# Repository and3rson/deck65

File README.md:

# Deck65

Homebrew 6502-based single-board computer with WiFi, built-in mechanical keyboard, uSD card adapter, I2C/SPI, EEPROM, & RTC.

- New discussion: <http://forum.6502.org/viewtopic.php?f=6&t=7682>
- Original thread (old SBC version): <http://forum.6502.org/viewtopic.php?f=12&t=7501>

Pull with `git pull --recurse-submodules`.

# Memory map

```
+--------------+-------+------------------+------+------------------------------------------+
| RANGE        | TYPE  | ADDR             | SIZE | Notes                                    |
+--------------+-------+------------------+------+------------------------------------------+
| $0000..$0FFF | RAM   | 0000------------ | 32 K | /EN = A15                                |
| $1000..$1FFF |       | 0001------------ |      | $0000..$1000 - zeropage & video buffer   |
| $2000..$2FFF |       | 0010------------ |      | $1000..$7FFF - programs from SD Card     |
| $3000..$3FFF |       | 0011------------ |      |                                          |
| $4000..$4FFF |       | 0100------------ |      |                                          |
| $5000..$5FFF |       | 0101------------ |      |                                          |
| $6000..$6FFF |       | 0110------------ |      |                                          |
| $7000..$7FFF |       | 0111------------ |      |                                          |
+--------------+-------+------------------+------+------------------------------------------+
| $8000..$8FFF | LOROM | 1000------------ | 16 K | /EN = NAND(A15, NAND(A14))               |
| $9000..$9FFF |       | 1001------------ |      | Contains OS ("MicroREPL")                |
| $A000..$AFFF |       | 1010------------ |      |                                          |
| $B000..$BFFF |       | 1011------------ |      |                                          |
+--------------+-------+------------------+------+------------------------------------------+
| $C000..$CFFF | N/C   | 1100------------ | 4 K  | Unused, may add extra '138 with /GA=/A13 |
+--------------+-------+------------------+------+------------------------------------------+
| $D000..$DFFF | I/O   | 1101------------ | 4 K  | G = A12, /GA = A13, /GB = NAND(A15, A14) |
|              |       | 1101-000-------- | 256B | $D000..$D0FF - RAM banking register      |
|              |       | 1101-001-------- | 256B | $D100..$D1FF - 6522 VIA                  |
|              |       | 1101-010-------- | 256B | $D200..$D2FF - 6551 ACIA                 |
|              |       | 1101-011-------- | 256B | $D300..$D3FF - T6963C LCD (240x64)       |
+--------------+-------+------------------+------+------------------------------------------+
| $E000..$EFFF | HIROM | 1110------------ | 8 K  | /EN = NAND(/NAND(A15, A14), A13)         |
| $F000..$FFFF |       | 1111------------ |      | Contains Kernel ("Kore")                 |
+--------------+-------+------------------+------+------------------------------------------+

LOROM (10xx) || HIROM (111x):
/EN = A15 && (/A14 || (A14 && A13))
/EN = NAND(A15, /A14 || /NAND(A14, A13))
/EN = NAND(A15, NAND(A14, NAND(A14, A13)))
```

# Features

- W65C02, 512 KB RAM (32KB visible to CPU, banked into 4 x 8 KB segments)
- 240x64 LCD display (T6963C)
- Built-in [mechanical PS/2 keyboard](./keyboard), powered by ATmega328P
- Internet! Works through ESP-01
- VIA W65C22<ins>N</ins>(6TPG-14)

  Provides:
  - SPI (used for Micro SD Card adapter)
  - I2C (used for RTC & EEPROM)
  - PS/2 host (used for built-in or external keyboard)
- ACIA W65C51<ins>N</ins>(6TPG-14)n

  Provides:
  - Communication with ESP-01
  - Communication with external devices through pin header
  > Note: I'm using NMOS-compatible versions of VIA & ACIA (<ins>N</ins> suffix) with open-drain /IRQ line.<br />
  > See http://archive.6502.org/datasheets/wdc_w65c22_sep_13_2010.pdf (page 25) for more details.
- Address decoder & underclocking - [ATF16V8B-15PU](./gal)
  > Main crystal is 16 MHz, and the CPU runs at either 8 MHz or 2 MHz.<br />
  > Reason for this is that T6963C LCD can only operate on up to 2.75 MHz.<br />
  > So when CPU needs to acccess the LCD, ATF16V8 divides clock speed by 4, bringing it down to 2 MHz.<br />
  > This is done by implementing a 2-bit counter using registered outputs.
- Memory banking: 74LS670
  > Entire RAM (first 32 KB) is divided into 4 x 8 KB segments.<br />
  > Each segment can use one of its own 16 banks.<br />
  > This allows to selectively bank parts of RAM in and out.<br />
  > Using a machine-tooled socket actually allows to connect JCO-8 or JCO-14 oscillators.
- Traco Power TSR 1-2450 (drop-in replacement for 7805)
  > It runs much cooler than L7805 since it's a switching regulator.<br />
  > I use them a lot, although they are not as cheap as 7805.

V2.0 schematic:

# ROM

Kernel code currently provides the following features:
- Simple REPL shell to monitor memory & run programs
- 128x64 LCD (through VIA)
- PS/2 keyboard (through VIA)
- Micro SD Card in SPI mode (through VIA)
- I2C & SPI support
- Basic FAT16 support - listing root folder, loading/executing programs

# Resources

- [Kicad files](./kicad) - <https://www.kicad.org/>
- [DipTrace PCBs](./diptrace) - <https://diptrace.com/>
- [Circuits](./circuits) (created with [Digital](https://github.com/hneemann/Digital))
- [ROM sources](./rom) (written in 6502 Assembly, requires [cc65](https://cc65.github.io/) compiler)
- [SD Card programs](./sdcard) (written in 6502 C, requires [cc65](https://cc65.github.io/) compiler)
- [Keyboard firmware](./keyboard) (written in C)
- [GAL stuff](./gal) (hexadecimal 7-segment decoder, address decoder, etc using GAL16V8/GAL20V8, includes `galasm` as submodule)
- [Composite video test](./compvid) using ATtiny45 (requires [avra](https://github.com/Ro5bert/avra))

# So what can you do with it?

Playing snake, for example:

# Credits & references
- [6502.org community](forum.6502.org/) - Limitless help & support
- https://www.masswerk.at/6502/6502_instruction_set.html
- https://github.com/4x1md/kicad_libraries - Mini-DIN-6 symbol & footprint
- http://39k.ca/reading-files-from-fat16/
- https://laughtonelectronics.com/Arcana/KimKlone/Kimklone_opcode_mapping.html - cool illegal NOPs
- https://octopart.componentsearchengine.com/part.php?partID=570717&ref=octopart - Aries 28-526-10 footprint
- https://github.com/daprice/keyswitches.pretty - MX switches
- https://components101.com/sites/default/files/component_datasheet/Micro-SD-Card-Module-Datasheet.pdf - MicroSD card module datasheet & dimensions
- http://static.cactus.io/docs/sensors/temp-humidity/mcp9808/25095A.pdf - MCP9808 I2C temperature sensor
- https://ww1.microchip.com/downloads/aemDocuments/documents/MPD/ProductDocuments/DataSheets/24AA512-24LC512-24FC512-512K-Bit-I2C-Serial-EEPROM-20001754Q.pdf

# Links
- 6502 Primer: http://wilsonminesco.com/6502primer/
- Address Selector: https://circuitverse.org/simulator/embed/6502-address-selector
- Read-Write Selector: https://circuitverse.org/simulator/embed/6502-read-write-selector
- SID (HVSC) format: https://gist.github.com/cbmeeks/2b107f0a8d36fc461ebb056e94b2f4d6

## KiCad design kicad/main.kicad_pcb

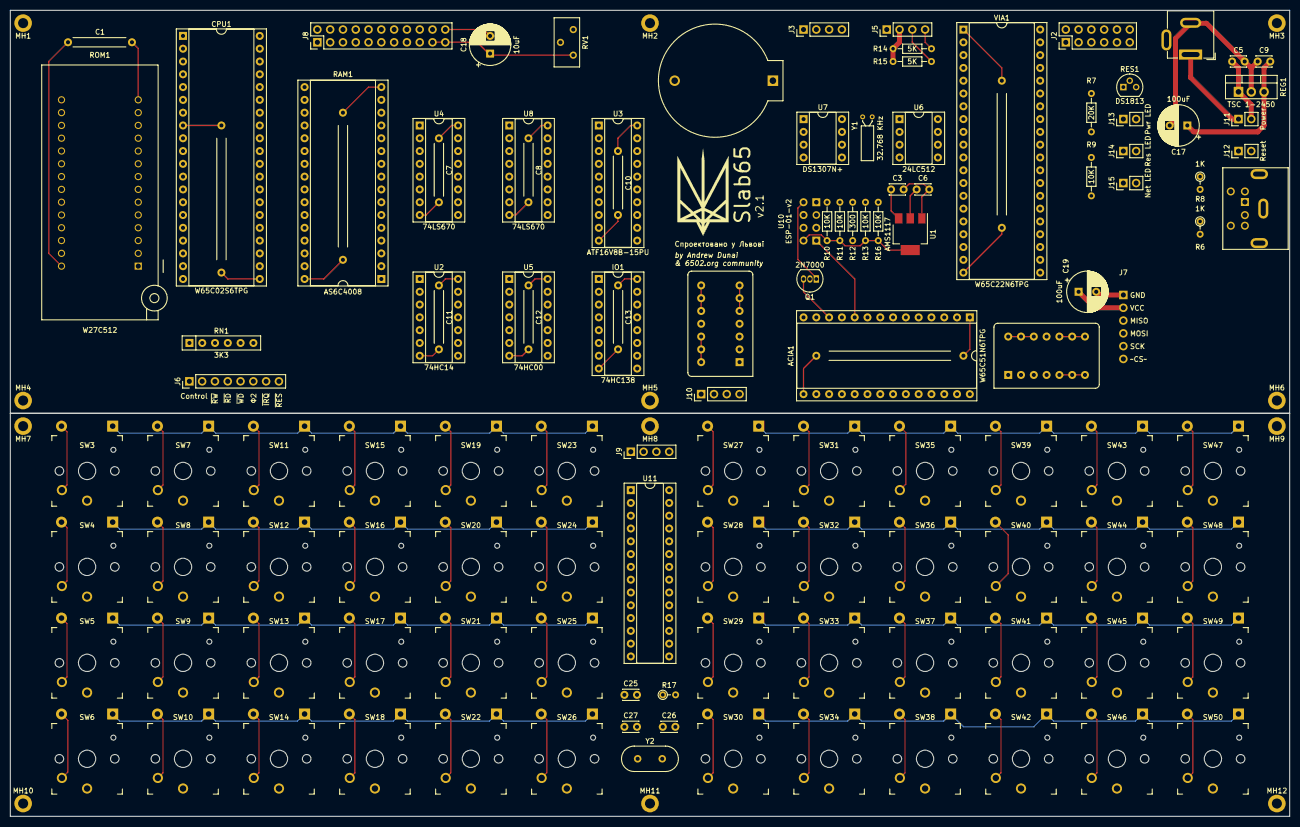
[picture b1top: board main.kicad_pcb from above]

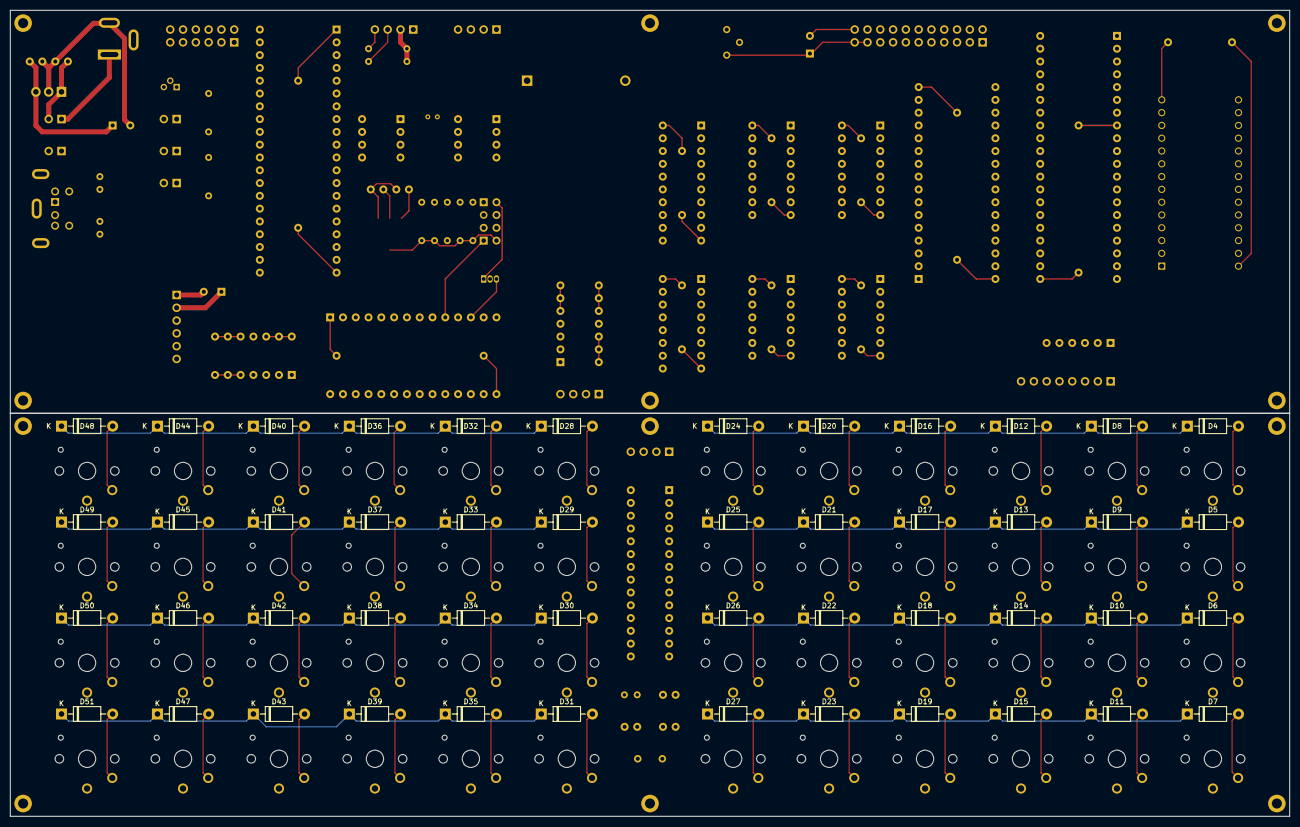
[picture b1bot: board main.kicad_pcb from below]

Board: 2 copper layers, 254.0 x 160.0 mm, 183 parts (48 on the bottom side), 164 nets.

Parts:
ACIA1: W65C51N6TPG; DIP-28_W15.24mm_Socket
BT1: CR2032; BatteryHolder_CR2032
C1, C7, C8, C10, C11, C12, C13: 0.1uF; C_Disc_Long
C2, C4, C14, C15: 0.1uF; C_Disc_VeryLong
C3, C5: 10uF; C_Disc_D3.0mm_W2.0mm_P2.50mm
C6: 22uF; C_Disc_D3.0mm_W2.0mm_P2.50mm
C9: 0.1uF; C_Disc_D3.0mm_W2.0mm_P2.50mm
C17, C19: 100uF; CP_Radial_D8.0mm_P3.50mm
C18: 10uF; CP_Radial_D8.0mm_P3.50mm
C25: 0,1uF; C_Disc_D3.0mm_W2.0mm_P2.50mm
C26, C27: 22pF; C_Disc_D3.0mm_W2.0mm_P2.50mm
CPU1: W65C02S6TPG; DIP-40_W15.24mm_Socket
D4, D5, D6, D7, D8, D9, D10, D11, D12, D13, D14, D15, D16, D17, D18, D19, D20, D21, D22, D23, D24, D25, D26, D27, D28, D29, D30, D31, D32, D33, D34, D35, D36, D37, D38, D39, D40, D41, D42, D43, D44, D45, D46, D47, D48, D49, D50, D51: 1N4001; D_DO-41_SOD81_P10.16mm_Horizontal
H1: LCD; LCD24064_silk
IO1: 74HC138; DIP-16_W7.62mm_Socket
J1: Jack-DC; BarrelJackEdge
J2: VIA_A; PinHeader_2x06_P2.54mm_Vertical
J3: UART; PinHeader_1x04_P2.54mm_Vertical
J5: I2C1; PinHeader_1x04_P2.54mm_Vertical
J6: Control; PinHeader_1x08_P2.54mm_Vertical
J7: uSD; MicroSD-Adapter
J8: LCD_Conn; PinHeader_2x11_P2.54mm_Vertical
J9, J10: Keyboard; PinHeader_1x04_P2.54mm_Vertical
J11: Power; PinHeader_1x02_P2.54mm_Vertical
J12: Reset; PinHeader_1x02_P2.54mm_Vertical
J13: Pwr LED; PinHeader_1x02_P2.54mm_Vertical
J14: Res LED; PinHeader_1x02_P2.54mm_Vertical
J15: Net LED; PinHeader_1x02_P2.54mm_Vertical
MH1, MH2, MH3, MH4, MH5, MH6, MH7, MH8, MH9, MH10, MH11, MH12: MountingHole; Hole_2x3.5
P1: Mini-DIN-6; Connector_Mini-DIN_Female_6Pin_2rows
Q1: 2N7000; TO-92_Inline
R6, R8: 1K; R_Axial_DIN0204_L3.6mm_D1.6mm_P2.54mm_Vertical
R7: 20K; R_Axial_DIN0204_L3.6mm_D1.6mm_P7.62mm_Horizontal
R9, R10, R11, R13, R16: 10K; R_Axial_DIN0204_L3.6mm_D1.6mm_P7.62mm_Horizontal
R12: 300; R_Axial_DIN0204_L3.6mm_D1.6mm_P7.62mm_Horizontal
R14, R15: 5K; R_Axial_DIN0204_L3.6mm_D1.6mm_P7.62mm_Horizontal
R17: 5K; R_Axial_DIN0204_L3.6mm_D1.6mm_P2.54mm_Vertical
RAM1: AS6C4008; DIP-32_W15.24mm_Socket
REG1: TSC 1-2450; TO-220-3_Vertical
RES1: DS1813; TO-92
RN1: 3K3; R_Array_SIP6
ROM1: W27C512; ZIF28
RV1: 10K; Potentiometer_Bourns_3296Y_Vertical
SW3, SW4, SW5, SW6, SW7, SW8, SW9, SW10, SW11, SW12, SW13, SW14, SW15, SW16, SW17, SW18, SW19, SW20, SW21, SW22, SW23, SW24, SW25, SW26, SW27, SW28, SW29, SW30, SW31, SW32, SW33, SW34, SW35, SW36, SW37, SW38, SW39, SW40, SW41, SW42, SW43, SW44, SW45, SW46, SW47, SW48, SW49, SW50: SW_Push; SW_PG1350
U1: AMS1117; SOT-223-3_TabPin2
U2: 74HC14; DIP-14_W7.62mm_Socket
U3: ATF16V8B-15PU; DIP-20_W7.62mm_Socket
U4, U8: 74LS670; DIP-16_W7.62mm_Socket
U5: 74HC00; DIP-14_W7.62mm_Socket
U6: 24LC512; DIP-8_W7.62mm_Socket
U7: DS1307N+; DIP-8_W7.62mm_Socket
U10: ESP-01-v2; ESP-01
U11: ATmega328-P; DIP-28_W7.62mm_Socket
VIA1: W65C22N6TPG; DIP-40_W15.24mm_Socket
X1: 16 MHz; Oscillator_DIP-8-14
X2: 1.8432 MHz; Oscillator_DIP-8-14
Y1: 32.768 KHz; Crystal_C26-LF_D2.1mm_L6.5mm_Horizontal
Y2: Crystal; Crystal_HC49-U_Vertical

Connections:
+3.3V: C6.1, Q1.2 (G), R10.2, R11.2, R13.2, R16.2, U1.2 (VO), U10.8 (VCC)
+5V: ACIA1.2 (CS1), ACIA1.15 (VCC), C1.1, C2.1, C3.1, C4.1, C7.1, C8.1, C9.2, C10.1, C11.1, C12.1, C13.1, C14.1, C15.1, C17.1, C18.1, C19.1, CPU1.8 (VDD), IO1.6 (E3), IO1.16 (VCC), J2.2, J3.2, J5.2, J6.2, J7.2, J8.3, J8.19, J8.21, J10.2, P1.4, R6.2, R7.1, R8.2, R14.2, R15.2, RAM1.32 (VCC), REG1.3 (VO), RES1.2 (VCC), RN1.1 (common), ROM1.28 (VCC), RV1.1, U1.3 (VI), U2.14 (VCC), U3.20 (VCC), U4.16 (VCC), U5.14 (VCC), U6.8 (VCC), U7.8 (VCC), U8.16 (VCC), VIA1.20 (VCC), VIA1.24 (CS1), X1.12, X1.13, X1.14 (Vcc), X2.12, X2.13, X2.14 (Vcc)
+5VA: C5.1, J11.2, REG1.1 (VI)
ACIACLK: ACIA1.6 (XTAL1), X2.8 (OUT), X2.9, X2.10
ACIARX: ACIA1.12 (RxD), J3.4, Q1.3 (D), R16.1
ACIATX: ACIA1.10 (TxD), J3.3, U10.1 (RX)
ACIA~EN: ACIA1.3 (~CS2), IO1.13 (O2)
A_{0}: ACIA1.13 (RS0), CPU1.9 (A0), J8.8, RAM1.12 (A0), ROM1.10 (A0), U4.14 (Wa), U8.5 (Ra), U8.14 (Wa), VIA1.38 (RS0)
A_{1}: ACIA1.14 (RS1), CPU1.10 (A1), RAM1.11 (A1), ROM1.9 (A1), U4.13 (Wb), U8.4 (Rb), U8.13 (Wb), VIA1.37 (RS1)
A_{2}: CPU1.11 (A2), RAM1.10 (A2), ROM1.8 (A2), VIA1.36 (RS2)
A_{3}: CPU1.12 (A3), RAM1.9 (A3), ROM1.7 (A3), VIA1.35 (RS3)
A_{4}: CPU1.13 (A4), RAM1.8 (A4), ROM1.6 (A4)
A_{5}: CPU1.14 (A5), RAM1.7 (A5), ROM1.5 (A5)
A_{6}: CPU1.15 (A6), RAM1.6 (A6), ROM1.4 (A6)
A_{7}: CPU1.16 (A7), RAM1.5 (A7), ROM1.3 (A7)
A_{8}: CPU1.17 (A8), IO1.1 (A0), RAM1.27 (A8), ROM1.25 (A8)
A_{9}: CPU1.18 (A9), IO1.2 (A1), RAM1.26 (A9), ROM1.24 (A9)
A_{10}: CPU1.19 (A10), IO1.3 (A2), RAM1.23 (A10), ROM1.21 (A10)
A_{11}: CPU1.20 (A11), RAM1.25 (A11), ROM1.23 (A11)
A_{12}: CPU1.22 (A12), RAM1.4 (A12), ROM1.2 (A12), U3.7 (I7)
A_{13}: CPU1.23 (A13), RAM1.28 (A13), ROM1.26 (A13), U3.6 (I6), U4.5 (Ra)
A_{14}: CPU1.24 (A14), RAM1.3 (A14), ROM1.27 (A14), U3.5 (I5), U4.4 (Rb)
A_{15}: CPU1.25 (A15), RAM1.22 (CE#), U3.4 (I4)
BANK~EN: IO1.15 (O0), U2.1
BANK~RD: U5.6, U8.11 (~Er)
BANK~WD: U4.12 (~Ew), U5.8, U8.12 (~Ew)
B_{0}: RAM1.31 (A15), U4.10 (Q1)
B_{1}: RAM1.2 (A16), U4.9 (Q2)
B_{2}: RAM1.30 (A17), U4.7 (Q3)
B_{3}: RAM1.1 (A18), U4.6 (Q4)
CLK: U3.1 (I1/CLK), X1.8 (OUT), X1.9, X1.10
COL1: SW3.1, SW4.1, SW5.1, SW6.1, SW27.1, SW28.1, SW29.1, SW30.1, U11.14 (PB0)
COL2: SW7.1, SW8.1, SW9.1, SW10.1, SW31.1, SW32.1, SW33.1, SW34.1, U11.15 (PB1)
COL3: SW11.1, SW12.1, SW13.1, SW14.1, SW35.1, SW36.1, SW37.1, SW38.1, U11.16 (PB2)
COL4: SW15.1, SW16.1, SW17.1, SW18.1, SW39.1, SW40.1, SW41.1, SW42.1, U11.17 (PB3)
COL5: SW19.1, SW20.1, SW21.1, SW22.1, SW43.1, SW44.1, SW45.1, SW46.1, U11.18 (PB4)
COL6: SW23.1, SW24.1, SW25.1, SW26.1, SW47.1, SW48.1, SW49.1, SW50.1, U11.19 (PB5)
CS: J7.6, VIA1.13 (PB3)
D_{0}: ACIA1.18 (D0), CPU1.33 (D0), J8.11, RAM1.13 (DQ0), ROM1.11 (D0), U4.15 (D1), U8.10 (Q1), U8.15 (D1), VIA1.33 (D0)
D_{1}: ACIA1.19 (D1), CPU1.32 (D1), J8.12, RAM1.14 (DQ1), ROM1.12 (D1), U4.1 (D2), U8.1 (D2), U8.9 (Q2), VIA1.32 (D1)
D_{2}: ACIA1.20 (D2), CPU1.31 (D2), J8.13, RAM1.15 (DQ2), ROM1.13 (D2), U4.2 (D3), U8.2 (D3), U8.7 (Q3), VIA1.31 (D2)
D_{3}: ACIA1.21 (D3), CPU1.30 (D3), J8.14, RAM1.17 (DQ3), ROM1.15 (D3), U4.3 (D4), U8.3 (D4), U8.6 (Q4), VIA1.30 (D3)
D_{4}: ACIA1.22 (D4), CPU1.29 (D4), J8.15, RAM1.18 (DQ4), ROM1.16 (D4), VIA1.29 (D4)
D_{5}: ACIA1.23 (D5), CPU1.28 (D5), J8.16, RAM1.19 (DQ5), ROM1.17 (D5), VIA1.28 (D5)
D_{6}: ACIA1.24 (D6), CPU1.27 (D6), J8.17, RAM1.20 (DQ6), ROM1.18 (D6), VIA1.27 (D6)
D_{7}: ACIA1.25 (D7), CPU1.26 (D7), J8.18, RAM1.21 (DQ7), ROM1.19 (D7), VIA1.26 (D7)
GND: ACIA1.1 (VSS), ACIA1.9 (~CTS), ACIA1.16 (~DCD), ACIA1.17 (~DSR), BT1.2 (-), C1.2, C2.2, C3.2, C4.2, C5.2, C6.2, C7.2, C8.2, C9.1, C10.2, C11.2, C12.2, C13.2, C14.2, C15.2, C17.2, C18.2, C19.2, CPU1.21 (VSS), IO1.4 (E1), IO1.8 (GND), J1.2, J2.1, J3.1, J5.1, J6.1, J7.1, J8.2, J8.22, J10.1, J12.1, J13.2, J14.2, J15.2, P1.3, RAM1.16 (VSS), REG1.2 (GND), RES1.3 (GND), ROM1.1 (A15), ROM1.14 (GND), U1.1 (ADJ), U2.7 (GND), U3.10 (GND), U3.11 (I10/~OE), U4.8 (GND), U4.11 (~Er), U5.7 (GND), U6.1 (A0), U6.2 (A1), U6.3 (A2), U6.4 (GND), U6.7 (WP), U7.4 (GND), U8.8 (GND), U10.4 (GND), VIA1.1 (VSS), X1.5, X1.6, X1.7 (GND), X2.5, X2.6, X2.7 (GND)
IO~EN: IO1.5 (E2), U3.19 (IO1)
I^{2}CCLK: J5.3, R15.1, U6.6 (SCL), U7.6 (SCL), VIA1.16 (PB6)
I^{2}CDATA: J5.4, R14.1, U6.5 (SDA), U7.5 (SDA), VIA1.15 (PB5)
LCD~EN: IO1.12 (O3), J8.7, U3.2 (I2)
MISO: J7.3, VIA1.10 (PB0)
MOSI: J7.4, VIA1.11 (PB1)
unnamed: BT1.1 (+), U7.3 (VBAT)
unnamed: CPU1.36 (BE), RN1.5 (R4)
unnamed: CPU1.2 (RDY), RN1.4 (R3)
unnamed: CPU1.38 (~SO), RN1.6 (R5)
unnamed: D4.2 (A), SW3.2
unnamed: D5.2 (A), SW4.2
unnamed: D6.2 (A), SW5.2
unnamed: D7.2 (A), SW6.2
unnamed: D8.2 (A), SW7.2
unnamed: D9.2 (A), SW8.2
unnamed: D10.2 (A), SW9.2
unnamed: D11.2 (A), SW10.2
unnamed: D12.2 (A), SW11.2
unnamed: D13.2 (A), SW12.2
unnamed: D14.2 (A), SW13.2
unnamed: D15.2 (A), SW14.2
unnamed: D16.2 (A), SW15.2
unnamed: D17.2 (A), SW16.2
unnamed: D18.2 (A), SW17.2
unnamed: D19.2 (A), SW18.2
unnamed: D20.2 (A), SW19.2
unnamed: D21.2 (A), SW20.2
unnamed: D22.2 (A), SW21.2
unnamed: D23.2 (A), SW22.2
unnamed: D24.2 (A), SW23.2
unnamed: D25.2 (A), SW24.2
unnamed: D26.2 (A), SW25.2
unnamed: D27.2 (A), SW26.2
unnamed: D28.2 (A), SW27.2
unnamed: D29.2 (A), SW28.2
unnamed: D30.2 (A), SW29.2
unnamed: D31.2 (A), SW30.2
unnamed: D32.2 (A), SW31.2
unnamed: D33.2 (A), SW32.2
unnamed: D34.2 (A), SW33.2
unnamed: D35.2 (A), SW34.2
unnamed: D36.2 (A), SW35.2
unnamed: D37.2 (A), SW36.2
unnamed: D38.2 (A), SW37.2
unnamed: D39.2 (A), SW38.2
unnamed: D40.2 (A), SW39.2
unnamed: D41.2 (A), SW40.2
unnamed: D42.2 (A), SW41.2
unnamed: D43.2 (A), SW42.2
unnamed: D44.2 (A), SW43.2
unnamed: D45.2 (A), SW44.2
unnamed: D46.2 (A), SW45.2
unnamed: D47.2 (A), SW46.2
unnamed: D48.2 (A), SW47.2
unnamed: D49.2 (A), SW48.2
unnamed: D50.2 (A), SW49.2
unnamed: D51.2 (A), SW50.2
unnamed: J2.3, VIA1.2 (PA0)
unnamed: J2.4, VIA1.3 (PA1)
unnamed: J2.5, VIA1.4 (PA2)
unnamed: J2.6, VIA1.5 (PA3)
unnamed: J2.7, VIA1.6 (PA4)
unnamed: J2.8, VIA1.7 (PA5)
unnamed: J2.9, VIA1.8 (PA6)
unnamed: J2.10, VIA1.9 (PA7)
unnamed: J2.11, VIA1.40 (CA1)
unnamed: J2.12, VIA1.39 (CA2)
unnamed: J8.4, RV1.2
unnamed: J8.20, RV1.3
unnamed: C25.1, C26.1, C27.1, J9.1, U11.8 (GND), U11.22 (GND)
unnamed: J9.2, R17.2, U11.7 (VCC), U11.20 (AVCC)
unnamed: J9.3, U11.12 (PD6)
unnamed: J9.4, U11.13 (PD7)
unnamed: J1.1, J11.1
unnamed: J13.1, R7.2
unnamed: J14.1, R9.2
unnamed: J15.1, R12.1
unnamed: P1.5, R6.1, U2.13
unnamed: Q1.1 (S), R13.1, U10.5 (TX)
unnamed: R9.1, U5.3
unnamed: U2.2, U5.4, U5.9
unnamed: U2.4, U5.5
unnamed: U2.6, U5.10
unnamed: U2.8, U2.11
unnamed: U2.9, U3.12 (IO8)
unnamed: U7.1 (X1), Y1.1
unnamed: U7.2 (X2), Y1.2
unnamed: R10.1, U10.6 (CH_EN)
unnamed: R11.1, U10.2 (GPIO0)
unnamed: R12.2, U10.3 (GPIO2)
unnamed: C25.2, U11.21 (AREF)
unnamed: C26.2, U11.9 (XTAL1/PB6), Y2.2
unnamed: C27.2, U11.10 (XTAL2/PB7), Y2.1
unnamed: R17.1, U11.1 (~RESET/PC6)
PHV: CPU1.37 (ϕ0), U2.10
PS2CLK: J10.3, U2.12, VIA1.19 (CB2)
PS2DATA: J10.4, P1.1, R8.1, VIA1.14 (PB4)
ROM~EN: ROM1.20 (~CE), U3.18 (IO2)
ROW1: D4.1 (K), D8.1 (K), D12.1 (K), D16.1 (K), D20.1 (K), D24.1 (K), U11.2 (PD0)
ROW2: D5.1 (K), D9.1 (K), D13.1 (K), D17.1 (K), D21.1 (K), D25.1 (K), U11.3 (PD1)
ROW3: D6.1 (K), D10.1 (K), D14.1 (K), D18.1 (K), D22.1 (K), D26.1 (K), U11.4 (PD2)
ROW4: D7.1 (K), D11.1 (K), D15.1 (K), D19.1 (K), D23.1 (K), D27.1 (K), U11.5 (PD3)
ROW5: D28.1 (K), D32.1 (K), D36.1 (K), D40.1 (K), D44.1 (K), D48.1 (K), U11.27 (PC4)
ROW6: D29.1 (K), D33.1 (K), D37.1 (K), D41.1 (K), D45.1 (K), D49.1 (K), U11.26 (PC3)
ROW7: D30.1 (K), D34.1 (K), D38.1 (K), D42.1 (K), D46.1 (K), D50.1 (K), U11.25 (PC2)
ROW8: D31.1 (K), D35.1 (K), D39.1 (K), D43.1 (K), D47.1 (K), D51.1 (K), U11.24 (PC1)
R~W: ACIA1.28 (R/~W), CPU1.34 (R/~W), J6.3, U3.8 (I8), VIA1.22 (R/~W)
SCK: J7.5, VIA1.12 (PB2)
SID~EN: IO1.11 (O4), U3.9 (I9)
VIA~EN: IO1.14 (O1), VIA1.23 (~CS2)
~IRQ: ACIA1.26 (~IRQ), CPU1.4 (~IRQ), J6.7, RN1.2 (R1), VIA1.21 (~IRQ)
~NMI: CPU1.6 (~NMI), RN1.3 (R2)
~RD: J6.4, J8.6, RAM1.24 (OE#), ROM1.22 (~OE), U2.3, U3.17 (I03)
~RES: ACIA1.4 (~RES), CPU1.40 (~RES), J6.8, J12.2, RES1.1 (~RST), U3.3 (I3), U5.1, U5.2, VIA1.34 (~RES)
~WD: J6.5, J8.5, RAM1.29 (WE#), U2.5, U3.16 (IO4)
Ф2: ACIA1.27 (ϕ2), J6.6, U3.15 (IO5), VIA1.25 (ϕ2)

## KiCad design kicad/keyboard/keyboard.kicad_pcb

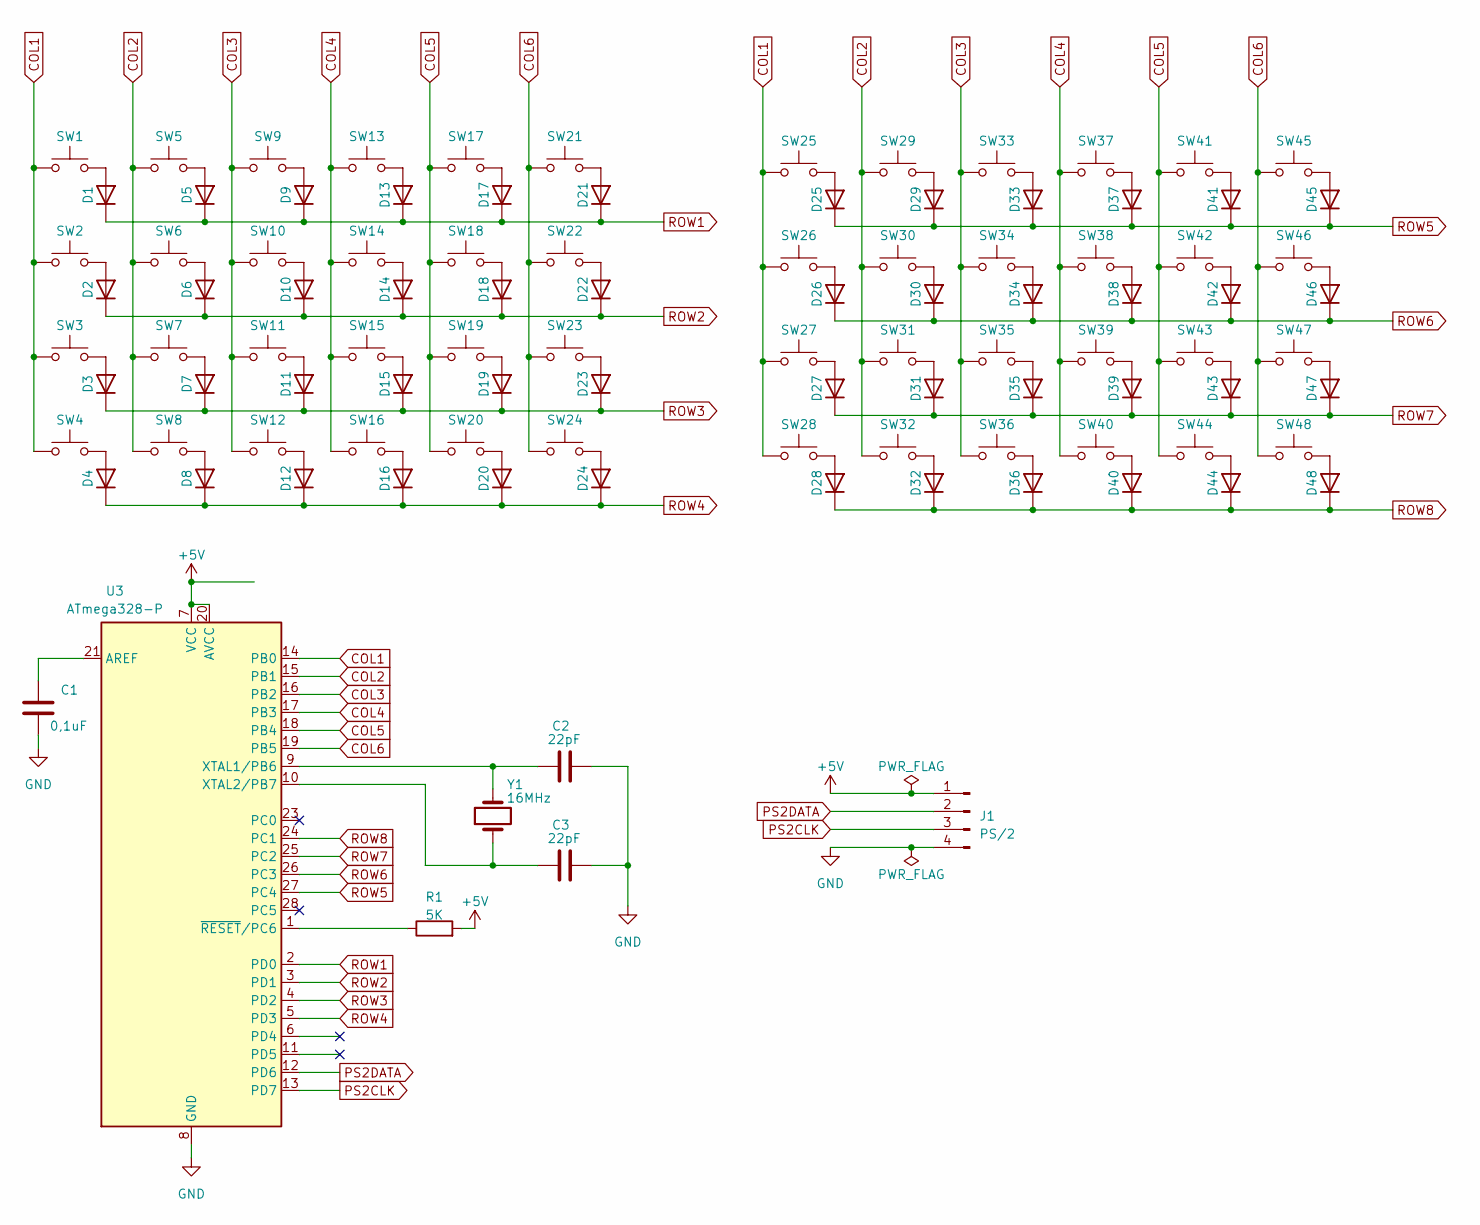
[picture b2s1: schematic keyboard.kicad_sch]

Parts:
C1: 0,1uF; C_Disc_D3.0mm_W2.0mm_P2.50mm
C2, C3: 22pF; C_Disc_D3.0mm_W2.0mm_P2.50mm
D1, D2, D3, D4, D5, D6, D7, D8, D9, D10, D11, D12, D13, D14, D15, D16, D17, D18, D19, D20, D21, D22, D23, D24, D25, D26, D27, D28, D29, D30, D31, D32, D33, D34, D35, D36, D37, D38, D39, D40, D41, D42, D43, D44, D45, D46, D47, D48: 1N4001; D_DO-41_SOD81_P10.16mm_Horizontal
J1: PS/2; PinHeader_1x04_P2.54mm_Vertical
R1: 5K; R_Axial_DIN0204_L3.6mm_D1.6mm_P2.54mm_Vertical
SW1, SW2, SW3, SW4, SW5, SW6, SW7, SW8, SW9, SW10, SW11, SW12, SW13, SW14, SW15, SW16, SW17, SW18, SW19, SW20, SW21, SW22, SW23, SW24, SW25, SW26, SW27, SW28, SW29, SW30, SW31, SW32, SW33, SW34, SW35, SW36, SW37, SW38, SW39, SW40, SW41, SW42, SW43, SW44, SW45, SW46, SW47, SW48: SW_Push; SW_PG1350
U3: ATmega328-P; DIP-28_W7.62mm_Socket
Y1: Crystal; Crystal_HC49-U_Vertical

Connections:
+5V: J1.1, R1.2, U3.7 (VCC), U3.20 (AVCC)
COL1: SW1.1, SW2.1, SW3.1, SW4.1, SW25.1, SW26.1, SW27.1, SW28.1, U3.14 (PB0)
COL2: SW5.1, SW6.1, SW7.1, SW8.1, SW29.1, SW30.1, SW31.1, SW32.1, U3.15 (PB1)
COL3: SW9.1, SW10.1, SW11.1, SW12.1, SW33.1, SW34.1, SW35.1, SW36.1, U3.16 (PB2)
COL4: SW13.1, SW14.1, SW15.1, SW16.1, SW37.1, SW38.1, SW39.1, SW40.1, U3.17 (PB3)
COL5: SW17.1, SW18.1, SW19.1, SW20.1, SW41.1, SW42.1, SW43.1, SW44.1, U3.18 (PB4)
COL6: SW21.1, SW22.1, SW23.1, SW24.1, SW45.1, SW46.1, SW47.1, SW48.1, U3.19 (PB5)
GND: C1.1, C2.1, C3.1, J1.4, U3.8 (GND), U3.22 (GND)
unnamed: D1.2 (A), SW1.2
unnamed: D2.2 (A), SW2.2
unnamed: D3.2 (A), SW3.2
unnamed: D4.2 (A), SW4.2
unnamed: D5.2 (A), SW5.2
unnamed: D6.2 (A), SW6.2
unnamed: D7.2 (A), SW7.2
unnamed: D8.2 (A), SW8.2
unnamed: D9.2 (A), SW9.2
unnamed: D10.2 (A), SW10.2
unnamed: D11.2 (A), SW11.2
unnamed: D12.2 (A), SW12.2
unnamed: D13.2 (A), SW13.2
unnamed: D14.2 (A), SW14.2
unnamed: D15.2 (A), SW15.2
unnamed: D16.2 (A), SW16.2
unnamed: D17.2 (A), SW17.2
unnamed: D18.2 (A), SW18.2
unnamed: D19.2 (A), SW19.2
unnamed: D20.2 (A), SW20.2
unnamed: D21.2 (A), SW21.2
unnamed: D22.2 (A), SW22.2
unnamed: D23.2 (A), SW23.2
unnamed: D24.2 (A), SW24.2
unnamed: D25.2 (A), SW25.2
unnamed: D26.2 (A), SW26.2
unnamed: D27.2 (A), SW27.2
unnamed: D28.2 (A), SW28.2
unnamed: D29.2 (A), SW29.2
unnamed: D30.2 (A), SW30.2
unnamed: D31.2 (A), SW31.2
unnamed: D32.2 (A), SW32.2
unnamed: D33.2 (A), SW33.2
unnamed: D34.2 (A), SW34.2
unnamed: D35.2 (A), SW35.2
unnamed: D36.2 (A), SW36.2
unnamed: D37.2 (A), SW37.2
unnamed: D38.2 (A), SW38.2
unnamed: D39.2 (A), SW39.2
unnamed: D40.2 (A), SW40.2
unnamed: D41.2 (A), SW41.2
unnamed: D42.2 (A), SW42.2
unnamed: D43.2 (A), SW43.2
unnamed: D44.2 (A), SW44.2
unnamed: D45.2 (A), SW45.2
unnamed: D46.2 (A), SW46.2
unnamed: D47.2 (A), SW47.2
unnamed: D48.2 (A), SW48.2
unnamed: C1.2, U3.21 (AREF)
unnamed: C2.2, U3.9 (XTAL1/PB6), Y1.2
unnamed: C3.2, U3.10 (XTAL2/PB7), Y1.1
unnamed: R1.1, U3.1 (~RESET/PC6)
PS2CLK: J1.3, U3.13 (PD7)
PS2DATA: J1.2, U3.12 (PD6)
ROW1: D1.1 (K), D5.1 (K), D9.1 (K), D13.1 (K), D17.1 (K), D21.1 (K), U3.2 (PD0)
ROW2: D2.1 (K), D6.1 (K), D10.1 (K), D14.1 (K), D18.1 (K), D22.1 (K), U3.3 (PD1)
ROW3: D3.1 (K), D7.1 (K), D11.1 (K), D15.1 (K), D19.1 (K), D23.1 (K), U3.4 (PD2)
ROW4: D4.1 (K), D8.1 (K), D12.1 (K), D16.1 (K), D20.1 (K), D24.1 (K), U3.5 (PD3)
ROW5: D25.1 (K), D29.1 (K), D33.1 (K), D37.1 (K), D41.1 (K), D45.1 (K), U3.27 (PC4)
ROW6: D26.1 (K), D30.1 (K), D34.1 (K), D38.1 (K), D42.1 (K), D46.1 (K), U3.26 (PC3)
ROW7: D27.1 (K), D31.1 (K), D35.1 (K), D39.1 (K), D43.1 (K), D47.1 (K), U3.25 (PC2)
ROW8: D28.1 (K), D32.1 (K), D36.1 (K), D40.1 (K), D44.1 (K), D48.1 (K), U3.24 (PC1)

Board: 2 copper layers, 103 parts (48 on the bottom side), 70 nets, no tracks yet.

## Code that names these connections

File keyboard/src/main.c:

/*
 * PS/2 keyboard implementation for ATmega328P
 * Supports multi-layer keymaps inspired by QMK firmware (https://qmk.fm/)
 * Keyboard is organized in 6x8 grid to save pins (versus 12x4 arrangement).
 * Matrix scanning order (diode direction) is row-to-column (rows are outputs, columns are inputs).
 * See ../../kicad/keyboard.kicad_sch for schematic
 */

#include <Arduino.h>

#include "scancodes.h"

#define COL_COUNT 6
#define ROW_COUNT 8
#define LAYERS    3

#define REPEAT_RATE       25
#define REPEAT_DELAY      200
#define DEBOUNCE_INTERVAL 10

#define PS2CLK  PIN_PD6
#define PS2DATA PIN_PD7

const uint8_t COLS[COL_COUNT] = {PIN_PB0, PIN_PB1, PIN_PB2, PIN_PB3, PIN_PB4, PIN_PB5};
const uint8_t ROWS[ROW_COUNT] = {PIN_PD0, PIN_PD1, PIN_PD2, PIN_PD3, PIN_PC4, PIN_PC3, PIN_PC2, PIN_PC1};
const uint16_t KEYMAP[LAYERS][COL_COUNT * ROW_COUNT] = {
    {
        // Layer 0
        //

        /* clang-format off */
        // Left half
        SC_TAB,   SC_Q,     SC_W,     SC_E,     SC_R,     SC_T,
        CC_LYR1,  SC_A,     SC_S,     SC_D,     SC_F,     SC_G,
        SC_LSHFT, SC_Z,     SC_X,     SC_C,     SC_V,     SC_B,
        SC_LCTRL, SC_ESC,   _____,    _____,    _____,    SC_SPACE,

        // Right half
        SC_Y,     SC_U,     SC_I,     SC_O,     SC_P,     SC_BKSPC,
        SC_H,     SC_J,     SC_K,     SC_L,     SC_SMCLN, SC_ENTER,
        SC_N,     SC_M,     SC_COMMA, SC_PRIOD, SC_SLASH, SC_LCTRL,
        SC_SPACE, CC_LYR2,  _____,    _____,    _____,    _____,
        /* clang-format on */
    },
    {
        // Layer 1
        //

        /* clang-format off */
        // Left half
        _____,    _____,    _____,    _____,    _____,    _____,
        _____,    _____,    _____,    _____,    _____,    _____,
        _____,    _____,    _____,    _____,    _____,    _____,
        _____,    _____,    _____,    _____,    _____,    _____,

        // Right half
        SC_MINUS, EC_PGUP,  EC_UP,    EC_PGDN,  _____,    EC_DEL,
        EC_HOME,  EC_LEFT,  EC_DOWN,  EC_RIGHT, SC_GRAVE, _____,
        EC_END,   SC_EQUAL, SC_LBRAC, SC_RBRAC, _____,    _____,
        _____,    _____,    _____,    _____,    _____,    _____,
        /* clang-format on */
    },
    {
        // Layer 2
        //

        /* clang-format off */
        // Left half
        _____,    SC_1,     SC_2,     SC_3,     SC_4,     SC_5,
        _____,    SC_F1,    SC_F2,    SC_F3,    SC_F4,    SC_F5,
        _____,    _____,    _____,    _____,    _____,    _____,
        _____,    _____,    _____,    _____,    _____,    _____,

        // Right half
        SC_6,     SC_7,     SC_8,     SC_9,     SC_0,     SC_F12,
        SC_F6,    SC_F7,    SC_F8,    SC_F9,    SC_F10,   SC_F11,
        _____,    _____,    _____,    _____,    _____,    _____,
        _____,    _____,    _____,    _____,    _____,    _____,
        /* clang-format on */
    },
};

#define INACTIVE 0xFF

// Defines which layer the key was pressed on and when.
typedef struct {
    // Layer on which the key was pressed, INACTIVE (0xFF) if not pressed.
    // We track this to properly break the key when it's released in case the layer has changed.
    uint8_t layer;
    // Is the key physically pressed at any point in time.
    // This is a raw value which is not debounced.
    // It's used to generate clean value for `layer` after debouncing.
    uint8_t phys;
    // When was the key pressed (for debouncing)
    uint32_t changedAt;
} key_state_t;

key_state_t keyStates[COL_COUNT * ROW_COUNT];
uint8_t currentLayer = 0;

// Last pressed key to repeat
uint16_t lastPressedKey = 0;
uint32_t nextRepeatAt = 0;

uint16_t handle_key(uint16_t keycode, bool isPressed);
void emit(uint16_t code, bool make);
void write(uint8_t code);
void writeBit(uint8_t bit);

// typedef struct {
//     uint8_t index;
//     uint16_t code;
//     uint32_t pressedAt;
// } pressed_key_info_t;

void setup() {
    pinMode(PS2CLK, OUTPUT);
    pinMode(PS2DATA, OUTPUT);
    digitalWrite(PS2CLK, HIGH);
    digitalWrite(PS2DATA, HIGH);
    for (uint8_t y = 0; y < ROW_COUNT; y++) {
        pinMode(ROWS[y], OUTPUT);
        digitalWrite(ROWS[y], HIGH);
    }
    for (uint8_t x = 0; x < COL_COUNT; x++) {
        pinMode(COLS[x], INPUT_PULLUP);
    }
    for (int i = 0; i < COL_COUNT * ROW_COUNT; i++) {
        keyStates[i].layer = INACTIVE;
        keyStates[i].phys = HIGH;
        keyStates[i].changedAt = 0;
    }

    // Send BAT
    delay(500);
    write(0xAA);
    delay(250);
}

// Scan the matrix
void loop() {
    if (lastPressedKey && millis() > nextRepeatAt) {
        emit(lastPressedKey, true);
        nextRepeatAt = millis() + 1000 / REPEAT_RATE;
    }

    for (uint8_t y = 0; y < ROW_COUNT; y++) {
        digitalWrite(ROWS[y], LOW);
        for (uint8_t x = 0; x < COL_COUNT; x++) {
            bool isPressed = digitalRead(COLS[x]) == LOW; // Key at (x;y) is pressed
            uint8_t index = y * COL_COUNT + x;
            key_state_t *keyState = &keyStates[index];
            bool wasPressed = keyState->phys;
            if (isPressed != wasPressed) {
                // Key state changed, start debouncing timer
                keyState->phys = isPressed;
                keyState->changedAt = millis();
            }

            // Check if debounce interval passed
            if (millis() - keyState->changedAt > DEBOUNCE_INTERVAL) {
                // Debounce interval passed
                bool wasActive = keyState->layer != INACTIVE;
                bool isActive = keyState->phys;
                if (isActive != wasActive) {
                    if (isActive) {
                        // Key pressed and is stable
                        keyState->layer = currentLayer;
                        lastPressedKey = handle_key(KEYMAP[currentLayer][index], true);
                        nextRepeatAt = millis() + REPEAT_DELAY;
                    } else {
                        // Key released and is stable
                        handle_key(KEYMAP[keyState->layer][index], false);
                        lastPressedKey = 0;
                        keyState->layer = INACTIVE;
                    }
                }
            }
        }
        digitalWrite(ROWS[y], HIGH);
    }
}

// Decide what to do when the key is pressed/released
uint16_t handle_key(uint16_t keycode, bool isPressed) {
    if (keycode == CC_LYR1) {
        currentLayer = isPressed ? 1 : 0;
        return 0;
    } else if (keycode == CC_LYR2) {
        currentLayer = isPressed ? 2 : 0;
        return 0;
    } else if (keycode) {
        emit(keycode, isPressed);
        return keycode;
    }
    return 0;
}

// Send PS/2 make/break sequence
void emit(uint16_t code, bool make) {
    if (!make) {
        write(0xF0);
    }
    if (code > 0xFF) {
        write((code >> 8) & 0xFF);
        code = code & 0xFF;
    }
    write(code);
}

// Write PS/2 packet
void write(uint8_t code) {
    writeBit(0); // Start bit
    uint8_t parity = 1;
    for (uint8_t i = 0; i < 8; i++) {
        // Data bits (LSB first)
        uint8_t bit = code & 0x01;
        writeBit(bit);
        parity += bit;
        code >>= 1;
    }
    writeBit(parity % 2);  // Parity bit
    writeBit(1);           // Stop bit
    delayMicroseconds(50); // Wait one entire clock cycle
}

// Write single bit with PS/2 clock cycle
void writeBit(uint8_t bit) {
    digitalWrite(PS2DATA, bit);
    delayMicroseconds(1);
    digitalWrite(PS2CLK, LOW);
    delayMicroseconds(25);
    digitalWrite(PS2CLK, HIGH);
    delayMicroseconds(25);
}

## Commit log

2023-02-19 Add address lines to 74HC138 (I/O address decoder)
2023-02-24 Final PCB layout (<10*10 cm)
2023-02-24 Add diptrace PCB
2023-02-24 Add V7 images
2023-02-24 Add Digital circuits & update README
2023-02-24 Add LEDs
2023-02-25 Add memory map to README, update diptrace PCB
2023-02-25 Add 3D model for ZIF socket - thanks Stefany Allaire: https://grabcad.com/library/28pins-zif-socket-placeholder-1
2023-02-25 Add 3D precision sockets
2023-02-25 Remove galasm
2023-02-25 Add galasm as submodule
2023-02-25 Rename LCD to sevenseg
2023-02-25 Update V8 schematics, move I/O to $Dxxx
2023-02-26 V9 & GAL stuff
2023-02-27 Add standoffs, update V9 render
2023-02-27 Add Traco Power TSR 1-2450
2023-02-27 Update image
2023-02-27 Damn github cache
2023-02-28 Update ROM code to be runnable in sim65, increase PCB spacing at borders
2023-02-28 Rename project to 65ad02
2023-02-28 Update PCB wording, remove outer rectangle
2023-03-07 WIP: Code cleanup, SID test
2023-03-07 Refactor some definitions from zp.s into lcd.s
2023-03-08 Improve LCD code, add basic SID support
2023-03-08 Cleanup segment names
2023-03-09 Add number printing operations (hex & binary repr)
2023-03-09 Add VIA free-running timer interrupts
2023-03-10 LCD via VIA
2023-03-10 LCD: Fricking finally.
2023-03-10 Add vdelay
2023-03-10 Fix timings
2023-03-11 Add PS/2 keyboard support
2023-03-11 Add shifted characters for PS/2 input
2023-03-11 Cleanup init.s
2023-03-12 V0.12: (PS/2 & 4-bit LCD with VIA), cleanup kicad libs
2023-03-12 Update README & images
2023-03-12 Add repl module, printmem command, lowercase hex parsing
2023-03-12 Rename repl to urepl
2023-03-12 Make jumptable cleaner, improve hex character parsing
2023-03-14 Add SD card support
2023-03-14 Code cleanup - scopes are neat
2023-03-14 Cleanup code, add docstrings
2023-03-14 Basic FAT16 functions (reading MBR & boot sector)
2023-03-15 Implement running programs from FAT16 SD card, add sample program
2023-03-16 Test illegal opcodes, update SPI pin assignments, update V12 PCB
2023-03-17 Refactor ROM code to use carry flag for errors.Add Aries low-profile ZIF socket to V12 board.
2023-03-18 Add lcd::printfz function. Cleanup macros.
2023-03-18 Add ATtiny45 assembly scaffold
2023-03-19 Update ATtiny PAL rendering timings
2023-03-25 V13 - 32K RAM + 24K ROM
2023-03-28 WIP: v0.14
2023-04-05 WIP: v0.15
2023-04-08 v0.15
2023-04-09 Fix PS/2 desync due to long SEI init
2023-04-09 Fix resistor values
2023-04-09 Add ctest
2023-04-10 Dual support for ASM & C programs. Took some time!
2023-04-10 Cleanup
2023-04-11 Load large files from FAT16, WIP for Maze
2023-04-12 Snake!
2023-04-13 Fix ACIA config
2023-04-13 V15 assembly images
2023-04-15 Increase clock speed to 8 MHz
2023-04-20 Add RTC & CR2032 battery, increase size of decoupling capacitors
2023-04-22 Implement I2C driver, add DS1307N RTC clock control program
2023-04-27 Attempt at modules and stuff
2023-04-28 Proper Kernel API for mixed C & ASM applications!
2023-04-29 Rewrite main process in C
2023-04-30 Add "system" and "exec"
2023-04-30 Add extended PS/2 scancodes (cursor keys)
2023-05-01 Implement passing arguments to programs via argc/argv
2023-05-01 Add directory listing & I2C scanner
2023-05-02 Reduce LCD delays for faster redraws
2023-05-02 Add "?" built-in (peek/poke)
2023-05-05 Add I2C routines for more efficient register read/write operations
2023-05-07 Add test for 24064 LCD
2023-05-08 WIP: V16
2023-05-09 WIP: V16 GAL stuff
2023-05-09 Replace address decoder & r/w qualifier with GAL
2023-05-10 Replace GAL20V8 with GAL(ATF)16V8
2023-05-10 Move power socket to top, move GAL down a bit
2023-05-11 Test program for T6963C display
2023-05-11 Generate top silk layer with Kicad
2023-05-12 Route /RST to ESP-01
2023-05-15 Update silkscreen
2023-05-15 Rename project to Deck65
2023-05-20 V16 with working display
2023-05-25 WIP: UART
2023-06-25 V17!
2023-07-02 Add support for 40x16 LCD
2023-07-04 Use tgi.h interface for screen resolution, add custom LCD characters
2023-07-06 Add ANSI escape handling to serial terminal client, add RPN calculator, add strtok, improve Makefile
2023-07-22 Cleanup code, add rw banking images, add tests dir
2023-07-22 v18: RAM banking, clock through inverters
2023-07-25 Cleanup code
2023-07-25 Update images
2023-07-26 WIP: v2.0 initial PCB
2023-07-27 WIP: v2.0 split board
2023-07-28 v2.0: Final PCB
2023-07-28 WIP: v2.0 case
2023-07-30 Update case
2023-08-02 Ignore nice65 formatting
2023-08-02 Cleanup case files
2023-08-06 Basic firmware for keyboard (ATmega328P)
2023-08-06 Add TODO
2023-08-07 Fix keyboard scanning code
2023-08-08 Add extended PS/2 keycodes, add support for keymaps with multiple layers
2023-08-11 Working keyboard firmware
2023-08-11 Update I/O map, add RAM bank register, add WifiModem as submodule
2023-08-11 Fix imports
2023-08-11 Add repeat feature to PS/2 keyboard firmware
2023-08-20 v2.1 PCB
2023-08-21 Initialize banks on startup (with '670)
2023-08-27 Add missing keys to keyboard
2023-08-27 v2.1 updates
2023-09-12 Update banking code
2023-09-13 Fix time app, fix at app telnet commands (needed passthrough in WiFiModem), fix exec return codes
2023-09-13 Fix cls return code
2023-09-14 Add keyboard debouncing
2023-09-14 Add missing \t char to PS/2 driver
2023-09-14 Add KLS7 switch, remove buttons from top panel
2023-09-15 Add GAL22V10 symbol
2023-09-15 Add .gitignore for librecad
2023-09-17 Add FreeCAD project, add v2.0 renders, add Kailh Choc 3D model
2023-09-18 Update case files
2023-09-20 Fix wrong LCD width in case files, add LCD model
2023-09-25 Fix symbols & LCD footprint
2023-10-01 Add 74LS148 & VPB
2023-10-03 Case images
2023-10-03 Add case images
2023-10-16 Add .envrc into docker during build
2023-11-28 SPI circuit
